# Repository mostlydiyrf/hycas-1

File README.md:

# hycas-1
Kicad files and documents for the Hycas-1 IF AGC amplifier designed by Wes Hayward, W7ZOI and Jeff Damm, WA7MLH.

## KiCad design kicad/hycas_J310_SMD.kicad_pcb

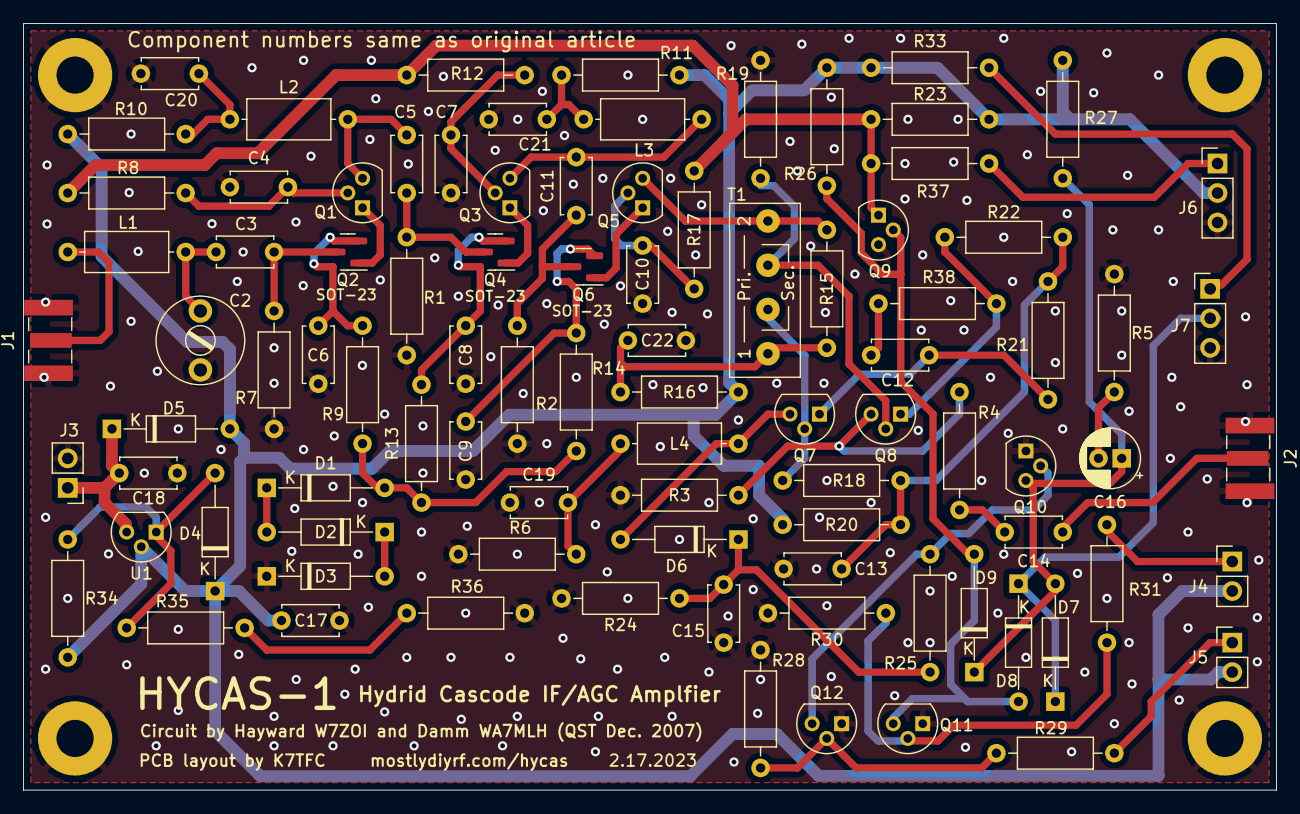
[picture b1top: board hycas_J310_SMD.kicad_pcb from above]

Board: 2 copper layers, 108.0 x 66.0 mm, 92 parts (0 on the bottom side), 52 nets.

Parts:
C2: 65; Capacitor_Trimmer_Ceramic_GKGxx015_Series
C3, C4, C5, C7, C10, C11, C15: .01; Ceramic_Disk_Capacitor_P5.00mm
C6, C8, C9, C12, C13, C14, C19, C20, C21, C22: 0.1; Ceramic_Disk_Capacitor_P5.00mm
C16: 4.7uF; CP_Radial_D5.0mm_P2.00mm
C17, C18: 0.22; Ceramic_Disk_Capacitor_P5.00mm
D1, D2, D3, D4, D5, D6, D7, D8, D9: D; D_DO-35_SOD27_P10.16mm_Horizontal
J1, J2: Phono_Jack_RCA; SMA_EdgeMount_0.062_Samtec
J3, J4, J5: Conn_01x02; PinHeader_1x02_P2.54mm_Vertical
J6, J7: Conn_01x03; PinHeader_1x03_P2.54mm_Vertical
L1: 6.8; L_Axial_L7.0mm_D3.3mm_P10.16mm_Horizontal_Fastron_MICC
L2, L3, L4: 47; L_Axial_L7.0mm_D3.3mm_P10.16mm_Horizontal_Fastron_MICC
Q1, Q3, Q5, Q10, Q11, Q12: 2N3904; TO-92L_Pin2_Offset
Q2, Q4, Q6: J310; SOT-23
Q7, Q8, Q9: 2N3906; TO-92L_Pin2_Offset
R1, R35: 1K; Resistor_Quarter_Watt_P10.16mm_Horizontal
R2, R25, R33: 2.2K; Resistor_Quarter_Watt_P10.16mm_Horizontal
R3: 51; Resistor_Quarter_Watt_P10.16mm_Horizontal
R4, R5: 0; Resistor_Quarter_Watt_P10.16mm_Horizontal
R6: 270; Resistor_Quarter_Watt_P10.16mm_Horizontal
R7, R15: 3.0K; Resistor_Quarter_Watt_P10.16mm_Horizontal
R8, R12, R17, R34: 220; Resistor_Quarter_Watt_P10.16mm_Horizontal
R9, R13, R14, R20: 180; Resistor_Quarter_Watt_P10.16mm_Horizontal
R10, R11, R16: 100; Resistor_Quarter_Watt_P10.16mm_Horizontal
R18: 4.7K; Resistor_Quarter_Watt_P10.16mm_Horizontal
R19, R28, R29, R30, R31, R37: 10K; Resistor_Quarter_Watt_P10.16mm_Horizontal
R21, R22: 680; Resistor_Quarter_Watt_P10.16mm_Horizontal
R23: 47K; Resistor_Quarter_Watt_P10.16mm_Horizontal
R24: 100K; Resistor_Quarter_Watt_P10.16mm_Horizontal
R26, R27: 1.5M; Resistor_Quarter_Watt_P10.16mm_Horizontal
R36: 330; Resistor_Quarter_Watt_P10.16mm_Horizontal
R38: 18; Resistor_Quarter_Watt_P10.16mm_Horizontal
T1: Transformer_RF_Small_Secondary; Toroid_Transformer_SM_Link_Secondary
U1: LM317L_TO92; TO-92L_Pin2_Offset

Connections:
+9V: C17.1, D4.1, D5.2, J4.2, J5.2, J6.2, R10.1, R11.1, R16.1, R20.2, R23.1, R26.1, R27.1, R33.2, R34.2, U1.2
+12V: C18.1, D5.1, J3.1, U1.3
GND: C2.2, C4.1, C6.2, C7.1, C8.2, C9.2, C10.1, C13.2, C15.1, C17.2, C18.2, C19.1, C20.2, C21.2, C22.2, D3.1, J1.2, J2.2, J3.2, J6.3, J7.3, Q9.3, Q10.1, Q11.1, Q12.1, R1.2, R2.2, R3.2, R5.1, R6.1, R7.2, R19.2, R24.1, R28.1, R30.1, R36.1
unnamed: C2.1, C3.2, L1.2
unnamed: C3.1, Q2.3, R7.1
unnamed: C4.2, Q1.2, R8.2
unnamed: C5.1, Q4.3, R1.1
unnamed: C5.2, L2.2, Q1.3
unnamed: C6.1, Q2.2, R9.1
unnamed: C7.2, Q3.2, R12.2
unnamed: C8.1, Q4.2, R13.1
unnamed: C9.1, Q6.2, R14.1
unnamed: C10.2, Q5.2, R17.2
unnamed: C11.1, Q6.3, R2.1
unnamed: C11.2, L3.2, Q3.3
unnamed: C12.1, R38.2
unnamed: C12.2, Q7.1, R21.2
unnamed: C13.1, R18.1, R20.1, R21.1, R22.1
unnamed: C14.1, J2.1
unnamed: C14.2, R4.1
unnamed: C15.2, D6.1, R24.2, R25.2
unnamed: C16.1, D7.2, D9.1, Q10.3, R27.2
unnamed: C16.2, R5.2
unnamed: C19.2, L4.2, R6.2
unnamed: C20.1, L2.1, R10.2
unnamed: C21.1, L3.1, R11.2
unnamed: C22.1, R15.1, R16.2, T1.1
unnamed: D1.1, D2.2
unnamed: D1.2, R9.2, R13.2, R14.2
unnamed: D2.1, D3.2
unnamed: D4.2, R34.1, R35.2, U1.1
unnamed: D6.2, L4.1, Q7.3
unnamed: D7.1, D8.1, J7.2
unnamed: D8.2, D9.2, Q9.2, Q11.3, R26.2
unnamed: J1.1, L1.1
unnamed: J4.1, R31.1
unnamed: J5.1, R29.1
unnamed: J6.1, R37.2
unnamed: J7.1, R33.1
unnamed: Q1.1, Q2.1
unnamed: Q3.1, Q4.1
unnamed: Q5.1, Q6.1
unnamed: Q5.3, R15.2, T1.2
unnamed: Q7.2, R18.2, T1.3
unnamed: Q8.1, R22.2, R38.1
unnamed: Q8.2, R19.1, T1.4
unnamed: Q8.3, R3.1, R4.2
unnamed: Q10.2, Q12.3, R25.1
unnamed: Q11.2, R30.2, R31.2
unnamed: Q12.2, R28.2, R29.2
unnamed: R35.1, R36.2
V-AGC: Q9.1, R8.1, R12.1, R17.1, R23.2, R37.1

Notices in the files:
kicad/hycas_J310_SMD.kicad_pcb:
CC BY-SA
